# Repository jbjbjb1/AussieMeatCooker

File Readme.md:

# Readme

The purpose of this project is to make a device to monitor bbq air and meat temperature to cook the perfect steak! The image below shows the current progress of the project - when a perfect steak is shown, this project is functional!

This project is currently functional and the temperature reading has an accuracy of +/-1 deg C. It uses bluetooth to communicate via bluetooth serial (e.g. android app: https://play.google.com/store/apps/details?id=de.kai_morich.serial_bluetooth_terminal&hl=en_AU&gl=US). This project initially started as an arduino based device and spring boarded off some great work done here: https://forum.arduino.cc/index.php?topic=231655.0, but since then it has moved to the ESP32 for a more compact design with inbuilt bluetooth functionality.

## Branches
* The "master" branch is the lastest functional ESP32 version of the meat cooker. 
* The "dev" branch is the working branch for new ESP32 features.
* The "arduino" branch is an archive of where this project got up to on the Arduino Uno.

## Next steps
* Get display working on ESP32 to show temperatures
* Refactor code
* Improve app interface
* 3D print case
* Improve reading range so air sensor can work down to 0 C (limited by ESP32 only being able to measure ADC from ~0.2V). 

## Items (all prices $AUD)
* 1 x meat sensor replacement Inkbird, $11.99 + $1.99, https://www.ebay.com.au/itm/PROBE-for-INKBIRD-IBT-4X-meat-thermometer-replacement-Accessories-REPLACE-sensor/222779014478?ssPageName=STRK%3AMEBIDX%3AIT&_trksid=p2057872.m2749.l2648
* 1 x bbq clip sensor replacement Inkbird, $10.99 + $1.99, https://www.ebay.com.au/itm/PROBE-Inkbird-cooking-thermometer-sensor-replacement-grill-clip-cable-replace/322770203997?ssPageName=STRK%3AMEBIDX%3AIT&_trksid=p2057872.m2749.l2648
* 2 x 2.5MM Stereo Chassis Socket, $1.85, https://www.jaycar.com.au/2-5mm-stereo-chassis-socket/p/PS0107
* 1 x ESP32 WOOROM-32 DEV board, ~$26
* 1 x breadboard PCB, ~$5
* 2 x 0.1 uF capacitor
* 1 x 1 kohm resistor
* 1 x 25 kohm resistor
* 1 x 40 pin female pin header
* Thin wire

## How to use
* Connect sensors by 2.5mm jacks
* Turn ESP32 on and connect to bluetooth
* Start cooking!

## Steps completed (newest on top)
* Fixed issue with sensors not reading correct temperature range
* Implement multisampling for esp32 adc (see example code here: https://github.com/espressif/esp-idf/blob/aaf12390eb14b95589acd98db5c268a2e56bb67e/examples/peripherals/adc/main/adc1_example_main.c#L72-L84 and explanation here: https://docs.espressif.com/projects/esp-idf/en/latest/esp32/api-reference/peripherals/adc.html#minimizing-noise)
* Check voltage divider resistances allow adequate analogue to digital conversion. For example, ESP32 can only measure between 0.2-3.08V effectively (which for the air sensor is 55C - 380C and meat sensor is <-10 C - >110 C). 
* Setup ESP32 ADC converter (details: https://docs.espressif.com/projects/esp-idf/en/latest/esp32/api-reference/peripherals/adc.html)
* Put on ESP32 board with bluetooth (similar to https://github.com/dereulenspiegel/ibbq-gateway)
* Added functionality for rate of change of temperature
* Sensors arrived, did calibration and calculated Steinhart-Hart model coefficients
* Arduino screen working (I2C to the 1602 LCD) and showing temperatures
* Got code working, used potentiometer to simulate different temperatures (as resistances)

## Backend steps
* cmd -> monitor to see what port
* pio: upload system image
* pio: upload and monitor

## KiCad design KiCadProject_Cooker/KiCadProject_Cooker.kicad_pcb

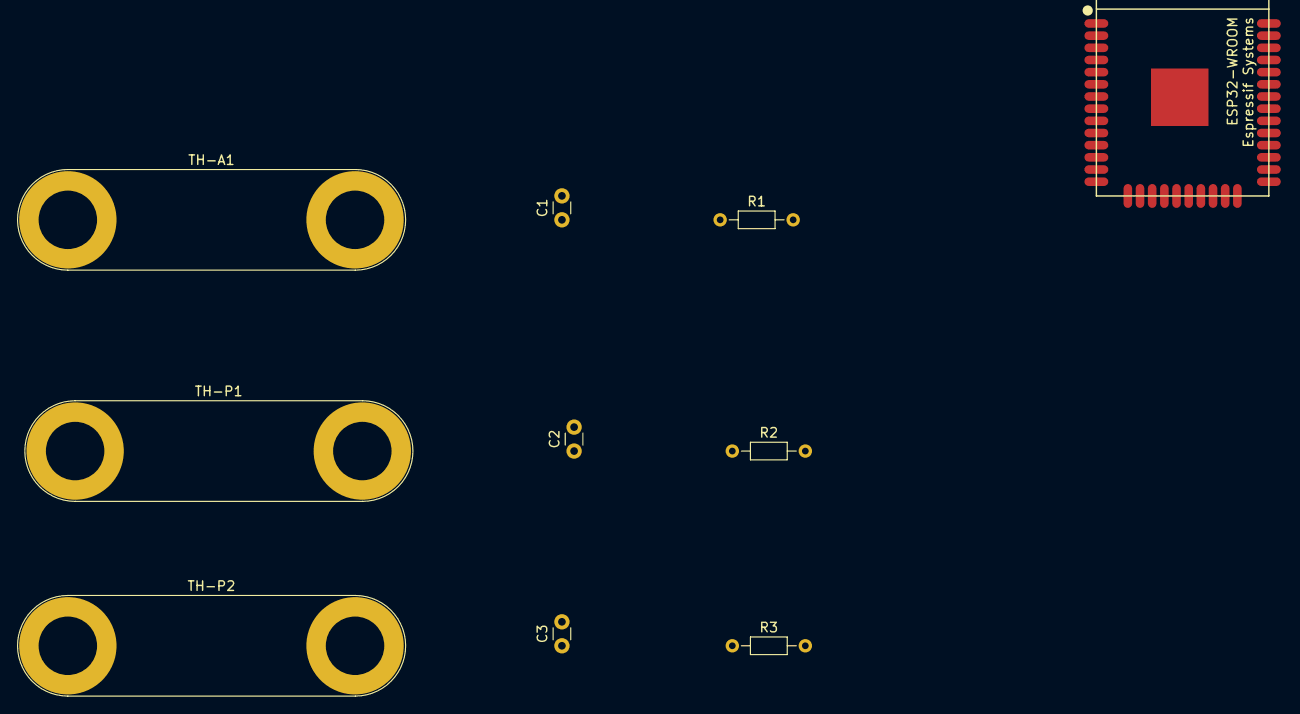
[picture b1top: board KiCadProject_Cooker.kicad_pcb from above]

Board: 2 copper layers, 10 parts (0 on the bottom side), 8 nets, no tracks yet.

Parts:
C1, C2, C3: 0.1uF; C_Disc_D3.0mm_W1.6mm_P2.50mm
R1: 1k; R_Axial_DIN0204_L3.6mm_D1.6mm_P7.62mm_Horizontal
R2, R3: 25k; R_Axial_DIN0204_L3.6mm_D1.6mm_P7.62mm_Horizontal
TH-A1: Thermistor; Banana_Jack_2Pin
TH-P1, TH-P2: Thermistor; Banana_Jack_2Pin
U1: ESP32-WROOM

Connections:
unnamed: C1.1, R1.1, TH-A1.2
unnamed: C1.2, U1.6
unnamed: C2.1, R2.1, TH-P1.2
unnamed: C2.2, U1.7
unnamed: C3.1, R3.1, TH-P2.2
unnamed: C3.2, U1.8
unnamed: R1.2, R2.2, R3.2, U1.1
unnamed: TH-A1.1, TH-P1.1, TH-P2.1, U1.2

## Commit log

2021-01-14 progressing voltage divider logic
2021-01-14 base code for voltage divider working
2021-01-15 determined optimum fixed res. for meat sensor
2021-01-15 Updated to do test with meat sensor
2021-01-16 working, testing on chicken
2021-01-29 Air and meat sensors working, rate showing
2021-01-30 Fixed probe labels, fixed error in temp rate code
2021-01-30 Basic plotting of log for temperature working
2021-02-05 now shows rate of change of temp
2021-02-05 Arduino prototype board pic
2021-02-05 updated readme with progress
2021-04-21 updates to plot data with python
2021-04-21 added kicad layout for esp32
2021-04-21 progress on setting up esp32 adc
2021-04-22 baisc working but not good temperature range
2021-04-22 working and functional
2021-04-22 functional project on arduino uno board before esp
2021-04-22 updated todo
2021-04-22 updated link for multisampling
2021-04-22 added todo
2021-04-24 Update readme before starting dev branch
2021-04-26 updated to do 64 samples each time
2021-04-26 pushed limit esp32 can read high air temp a little
2021-06-16 fixed issue cutting down range
2021-06-16 working well with rate of change of temp
2024-12-24 re-arrange folder to have files at top level
2024-12-27 work in progress re-factoring
2024-12-29 rough code ready
2024-12-29 fixed some errors
2024-12-29 working for terminal
2024-12-29 code working and functional
2024-12-30 index.html has banner for offline and table for snapshots
